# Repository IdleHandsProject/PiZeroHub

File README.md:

# PiZeroHub
USB Hub specifically designed for the Raspberry Pi Zero.

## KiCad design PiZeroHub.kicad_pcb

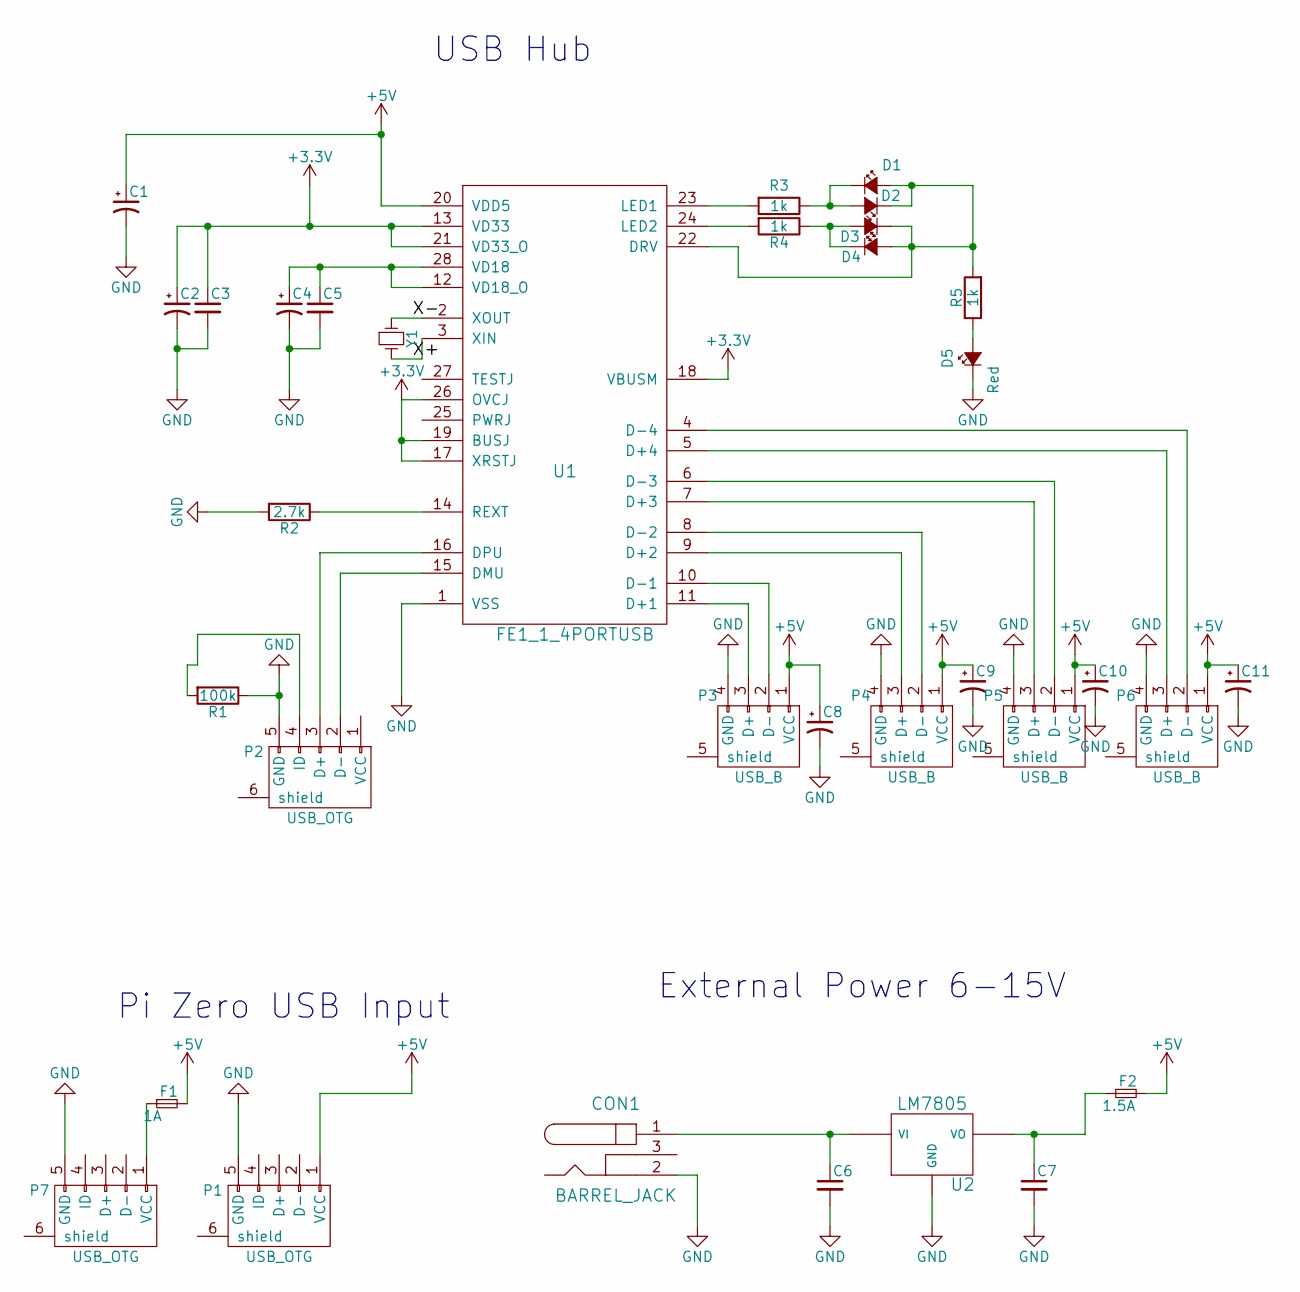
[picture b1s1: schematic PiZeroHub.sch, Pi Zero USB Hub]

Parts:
C1, C2, C4: 10uF; c_1206
C3, C5, C7: 0.1uF; C_0402_Hand
C6: 0.33uF; C_0402_Hand
C8, C9, C10, C11: 100uF; c_elec_5x5.3
CON1: BARREL_JACK
D1, D2, D3, D4: Green; LED-0603
D5: Red; LED-0603
F1: 1A; Fuse_SMD1206_Wave
F2: 1.5A; Fuse_SMD1206_Wave
P1, P2: USB_OTG; USB_Micro-B_Vert_OTG
P3, P4, P5, P6: USB_B; USB_A_Vert
P7: USB_OTG; USB_Micro-B
R1: 100k; R_0402_Hand
R2: 2.7k; R_0402_Hand
R3, R4, R5: 1k; R_0402_Hand
U1: FE1_1_4PORTUSB; SSOP-20
U2: LM7805; sot223
Y1: Crystal_Small; crystal_smd_5x3.2mm

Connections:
+3V3: C2.1, C3.1, U1.13 (VD33), U1.17 (XRSTJ), U1.18 (VBUSM), U1.19 (BUSJ), U1.21 (VD33_O), U1.26 (OVCJ)
+5V: C1.1, C8.1, C9.1, C10.1, C11.1, F1.2, F2.2, P1.1 (VCC), P3.1 (VCC), P4.1 (VCC), P5.1 (VCC), P6.1 (VCC), U1.20 (VDD5)
/X+: U1.3 (XIN), Y1.2
/X-: U1.2 (XOUT), Y1.1
GND: C1.2, C2.2, C3.2, C4.2, C5.2, C6.2, C7.2, C8.2, C9.2, C10.2, C11.2, CON1.2, D5.1 (K), P1.5 (GND), P2.5 (GND), P3.4 (GND), P4.4 (GND), P5.4 (GND), P6.4 (GND), P7.5 (GND), R1.1, R2.2, U1.1 (VSS), U2.1 (GND)
unnamed: C4.1, C5.1, U1.12 (VD18_O), U1.28 (VD18)
unnamed: C6.1, CON1.1, U2.3 (VI)
unnamed: C7.1, F2.1, U2.2 (VO)
unnamed: D1.1 (K), D2.2 (A), R3.1
unnamed: D1.2 (A), D2.1 (K), D3.1 (K), D4.2 (A), R5.2, U1.22 (DRV)
unnamed: D3.2 (A), D4.1 (K), R4.1
unnamed: D5.2 (A), R5.1
unnamed: F1.1, P7.1 (VCC)
unnamed: P2.2 (D-), U1.15 (DMU)
unnamed: P2.3 (D+), U1.16 (DPU)
unnamed: P2.4 (ID), R1.2
unnamed: P3.2 (D-), U1.10 (D-1)
unnamed: P3.3 (D+), U1.11 (D+1)
unnamed: P4.2 (D-), U1.8 (D-2)
unnamed: P4.3 (D+), U1.9 (D+2)
unnamed: P5.2 (D-), U1.6 (D-3)
unnamed: P5.3 (D+), U1.7 (D+3)
unnamed: P6.2 (D-), U1.4 (D-4)
unnamed: P6.3 (D+), U1.5 (D+4)
unnamed: R2.1, U1.14 (REXT)
unnamed: R3.2, U1.23 (LED1)
unnamed: R4.2, U1.24 (LED2)

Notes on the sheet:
Pi Zero USB Input
External Power 6-15V
USB Hub

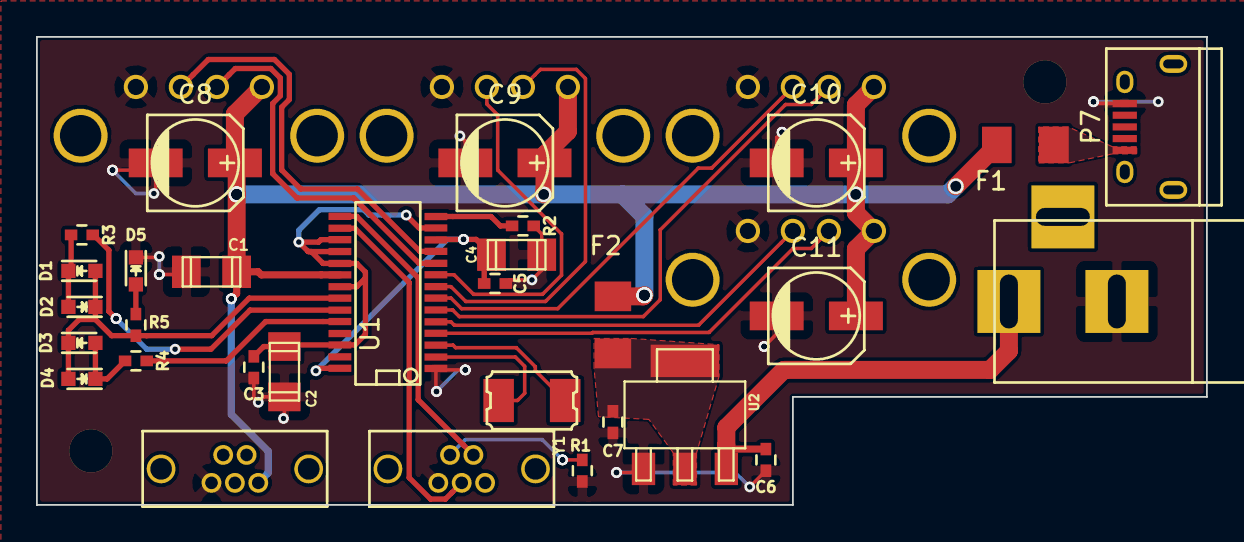
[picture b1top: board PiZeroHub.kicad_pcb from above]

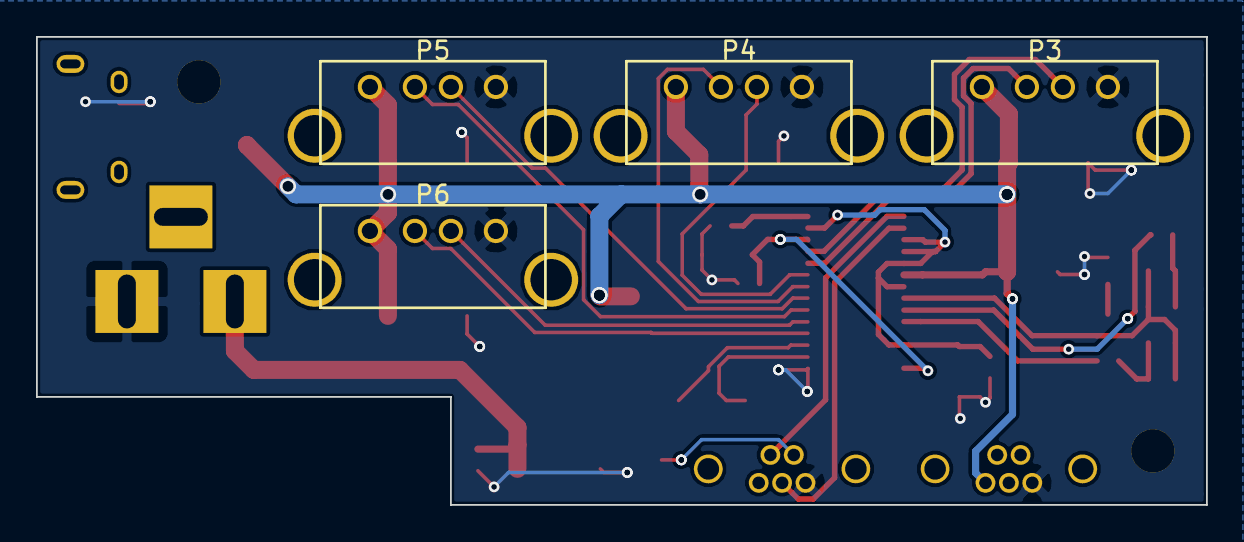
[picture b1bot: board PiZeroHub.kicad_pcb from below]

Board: 2 copper layers, 65.0 x 26.0 mm, 34 parts (4 on the bottom side), 27 nets.

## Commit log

2016-01-12 First Push
2016-01-14 Finish first version
2016-02-10 latest version, new USB part and footprint, cleaner design
